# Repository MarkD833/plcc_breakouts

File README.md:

# PLCC Breakout Boards
I recently got back into designing some retro computer boards using an 8085, Z80, 68008 and 8051 chips. In order to quickly get to version 1 of a board, I needed to sort out the wiring. I created these breakout boards to allow me to patch any chip in a PLCC44, PLCC52, PLCC68 or PLCC84 package onto my memory kickstarter board (includes ROM, RAM, UART, clock, LEDs etc) to allow for rapid prototyping witout committing to a PCB design first.

There are currently 4 breakout boards.

## PLCC44 Breakout board

## PLCC52 Breakout board

## PLCC68 Breakout board

## PLCC84 Breakout board

For each breakout board, each pin on the PLCC socket is broken out into 2 pinheader (or pinsocket) contacts. There are 8 ground pins that connect to the copper pour BUT do not connect to any pins on the PLCC socket. There is no decoupling provided on the breakout board as the power and ground pins are specific to the actual device being used. 

Please see the boards folder for the Kicad design files.

## Version History

* 1.0
    * Initial Release

## License

This project is licensed under the GNU General Public License v3.0 - see the LICENSE.md file for details

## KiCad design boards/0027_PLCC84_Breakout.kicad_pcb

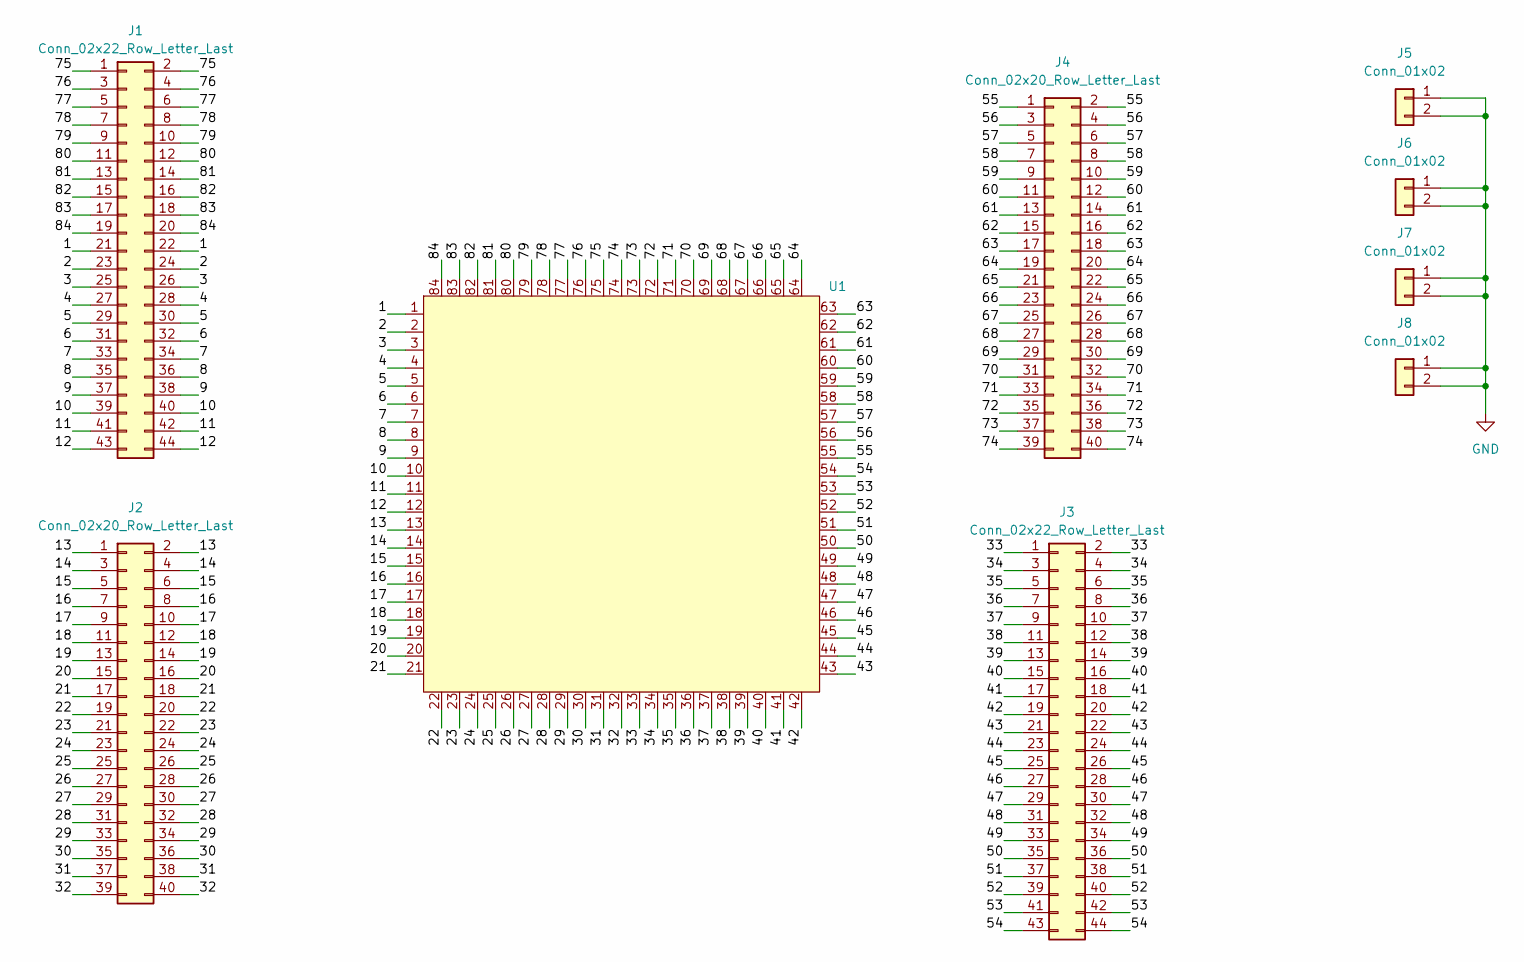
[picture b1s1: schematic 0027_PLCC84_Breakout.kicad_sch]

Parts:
J1, J3: Conn_02x22_Row_Letter_Last; PinSocket_2x22_P2.54mm_Vertical
J2, J4: Conn_02x20_Row_Letter_Last; PinSocket_2x20_P2.54mm_Vertical
J5, J6, J7, J8: Conn_01x02; PinHeader_1x02_P2.54mm_Vertical
U1: PLCC-84_THT-Socket

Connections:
/1: J1.21, J1.22, U1.1
/2: J1.23, J1.24, U1.2
/3: J1.25, J1.26, U1.3
/4: J1.27, J1.28, U1.4
/5: J1.29, J1.30, U1.5
/6: J1.31, J1.32, U1.6
/7: J1.33, J1.34, U1.7
/8: J1.35, J1.36, U1.8
/9: J1.37, J1.38, U1.9
/10: J1.39, J1.40, U1.10
/11: J1.41, J1.42, U1.11
/12: J1.43, J1.44, U1.12
/13: J2.1, J2.2, U1.13
/14: J2.3, J2.4, U1.14
/15: J2.5, J2.6, U1.15
/16: J2.7, J2.8, U1.16
/17: J2.9, J2.10, U1.17
/18: J2.11, J2.12, U1.18
/19: J2.13, J2.14, U1.19
/20: J2.15, J2.16, U1.20
/21: J2.17, J2.18, U1.21
/22: J2.19, J2.20, U1.22
/23: J2.21, J2.22, U1.23
/24: J2.23, J2.24, U1.24
/25: J2.25, J2.26, U1.25
/26: J2.27, J2.28, U1.26
/27: J2.29, J2.30, U1.27
/28: J2.31, J2.32, U1.28
/29: J2.33, J2.34, U1.29
/30: J2.35, J2.36, U1.30
/31: J2.37, J2.38, U1.31
/32: J2.39, J2.40, U1.32
/33: J3.1, J3.2, U1.33
/34: J3.3, J3.4, U1.34
/35: J3.5, J3.6, U1.35
/36: J3.7, J3.8, U1.36
/37: J3.9, J3.10, U1.37
/38: J3.11, J3.12, U1.38
/39: J3.13, J3.14, U1.39
/40: J3.15, J3.16, U1.40
/41: J3.17, J3.18, U1.41
/42: J3.19, J3.20, U1.42
/43: J3.21, J3.22, U1.43
/44: J3.23, J3.24, U1.44
/45: J3.25, J3.26, U1.45
/46: J3.27, J3.28, U1.46
/47: J3.29, J3.30, U1.47
/48: J3.31, J3.32, U1.48
/49: J3.33, J3.34, U1.49
/50: J3.35, J3.36, U1.50
/51: J3.37, J3.38, U1.51
/52: J3.39, J3.40, U1.52
/53: J3.41, J3.42, U1.53
/54: J3.43, J3.44, U1.54
/55: J4.1, J4.2, U1.55
/56: J4.3, J4.4, U1.56
/57: J4.5, J4.6, U1.57
/58: J4.7, J4.8, U1.58
/59: J4.9, J4.10, U1.59
/60: J4.11, J4.12, U1.60
/61: J4.13, J4.14, U1.61
/62: J4.15, J4.16, U1.62
/63: J4.17, J4.18, U1.63
/64: J4.19, J4.20, U1.64
/65: J4.21, J4.22, U1.65
/66: J4.23, J4.24, U1.66
/67: J4.25, J4.26, U1.67
/68: J4.27, J4.28, U1.68
/69: J4.29, J4.30, U1.69
/70: J4.31, J4.32, U1.70
/71: J4.33, J4.34, U1.71
/72: J4.35, J4.36, U1.72
/73: J4.37, J4.38, U1.73
/74: J4.39, J4.40, U1.74
/75: J1.1, J1.2, U1.75
/76: J1.3, J1.4, U1.76
/77: J1.5, J1.6, U1.77
/78: J1.7, J1.8, U1.78
/79: J1.9, J1.10, U1.79
/80: J1.11, J1.12, U1.80
/81: J1.13, J1.14, U1.81
/82: J1.15, J1.16, U1.82
/83: J1.17, J1.18, U1.83
/84: J1.19, J1.20, U1.84
GND: J5.1, J5.2, J6.1, J6.2, J7.1, J7.2, J8.1, J8.2

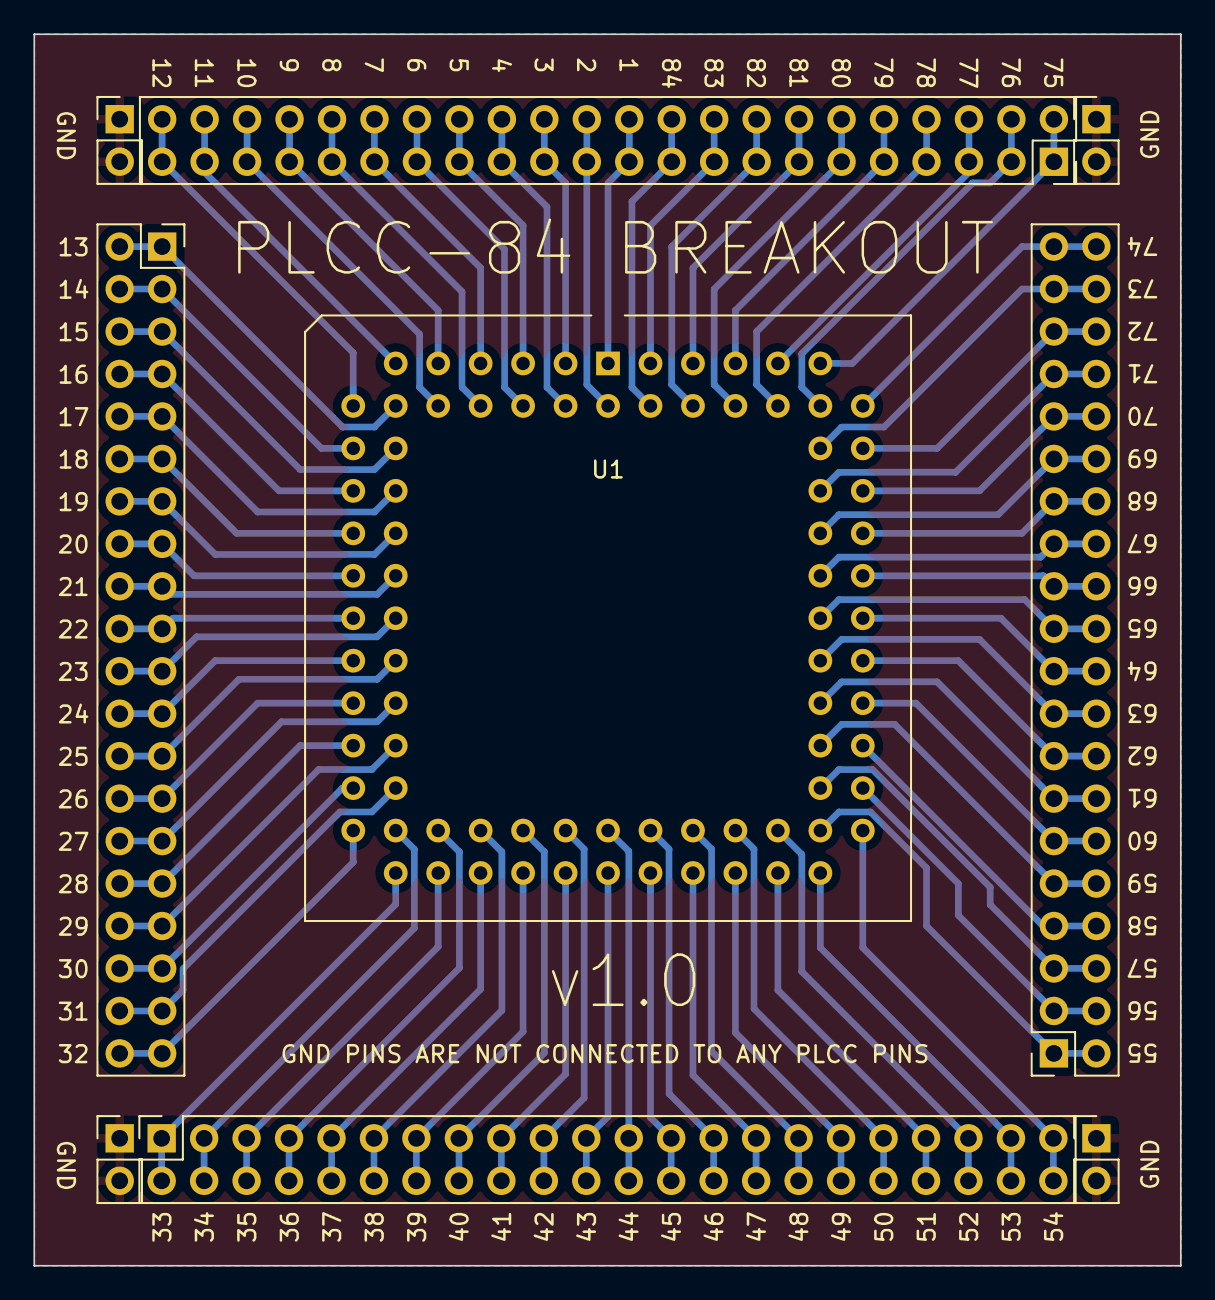
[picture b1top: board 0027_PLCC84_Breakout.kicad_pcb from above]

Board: 2 copper layers, 68.6 x 73.7 mm, 9 parts (0 on the bottom side), 85 nets.

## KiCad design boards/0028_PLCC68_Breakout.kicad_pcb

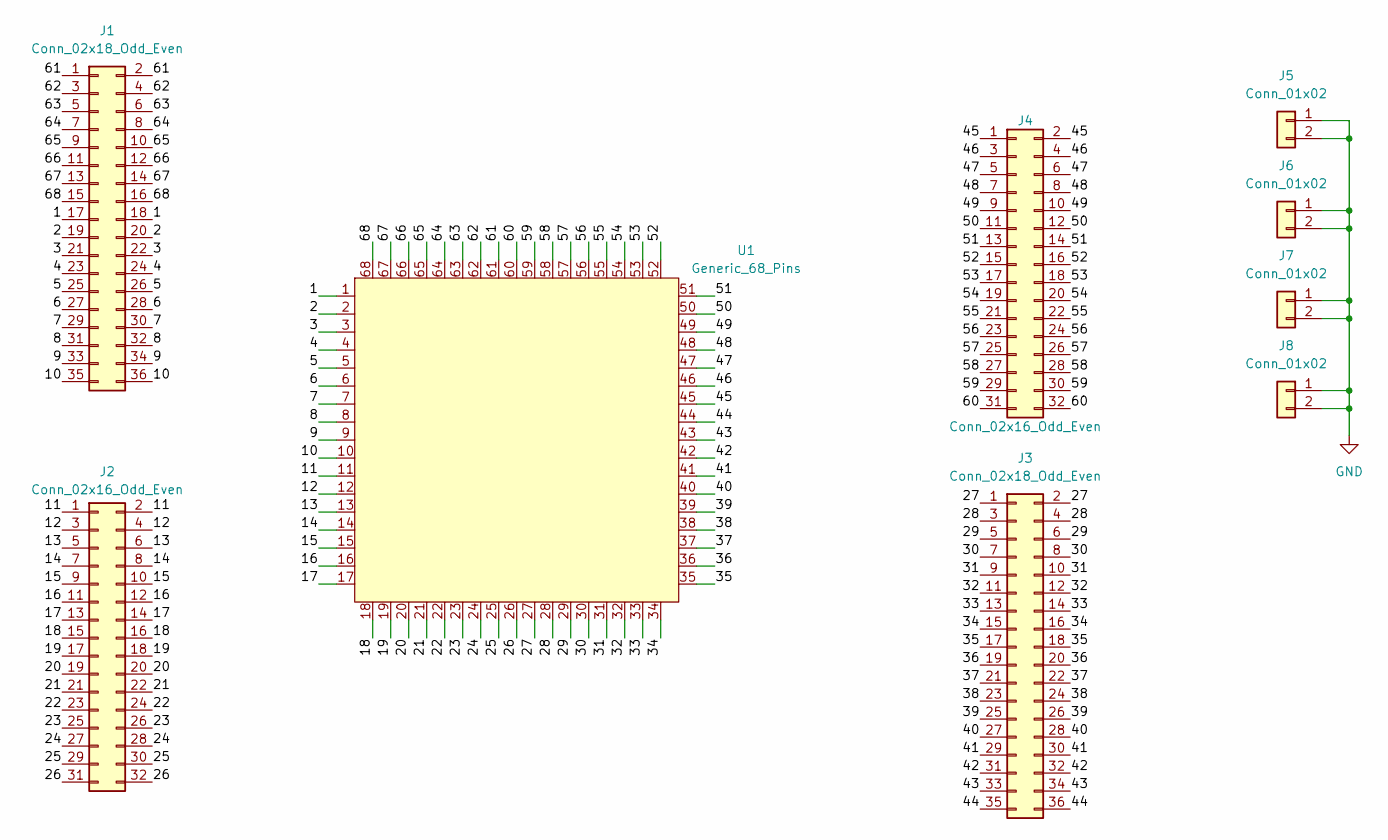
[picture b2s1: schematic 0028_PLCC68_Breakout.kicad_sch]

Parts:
J1, J3: Conn_02x18_Odd_Even; PinSocket_2x18_P2.54mm_Vertical
J2, J4: Conn_02x16_Odd_Even; PinSocket_2x16_P2.54mm_Vertical
J5, J6, J7, J8: Conn_01x02; PinHeader_1x02_P2.54mm_Vertical
U1: Generic_68_Pins; PLCC-68_THT-Socket

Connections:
/1: J1.17, J1.18, U1.1
/2: J1.19, J1.20, U1.2
/3: J1.21, J1.22, U1.3
/4: J1.23, J1.24, U1.4
/5: J1.25, J1.26, U1.5
/6: J1.27, J1.28, U1.6
/7: J1.29, J1.30, U1.7
/8: J1.31, J1.32, U1.8
/9: J1.33, J1.34, U1.9
/10: J1.35, J1.36, U1.10
/11: J2.1, J2.2, U1.11
/12: J2.3, J2.4, U1.12
/13: J2.5, J2.6, U1.13
/14: J2.7, J2.8, U1.14
/15: J2.9, J2.10, U1.15
/16: J2.11, J2.12, U1.16
/17: J2.13, J2.14, U1.17
/18: J2.15, J2.16, U1.18
/19: J2.17, J2.18, U1.19
/20: J2.19, J2.20, U1.20
/21: J2.21, J2.22, U1.21
/22: J2.23, J2.24, U1.22
/23: J2.25, J2.26, U1.23
/24: J2.27, J2.28, U1.24
/25: J2.29, J2.30, U1.25
/26: J2.31, J2.32, U1.26
/27: J3.1, J3.2, U1.27
/28: J3.3, J3.4, U1.28
/29: J3.5, J3.6, U1.29
/30: J3.7, J3.8, U1.30
/31: J3.9, J3.10, U1.31
/32: J3.11, J3.12, U1.32
/33: J3.13, J3.14, U1.33
/34: J3.15, J3.16, U1.34
/35: J3.17, J3.18, U1.35
/36: J3.19, J3.20, U1.36
/37: J3.21, J3.22, U1.37
/38: J3.23, J3.24, U1.38
/39: J3.25, J3.26, U1.39
/40: J3.27, J3.28, U1.40
/41: J3.29, J3.30, U1.41
/42: J3.31, J3.32, U1.42
/43: J3.33, J3.34, U1.43
/44: J3.35, J3.36, U1.44
/45: J4.1, J4.2, U1.45
/46: J4.3, J4.4, U1.46
/47: J4.5, J4.6, U1.47
/48: J4.7, J4.8, U1.48
/49: J4.9, J4.10, U1.49
/50: J4.11, J4.12, U1.50
/51: J4.13, J4.14, U1.51
/52: J4.15, J4.16, U1.52
/53: J4.17, J4.18, U1.53
/54: J4.19, J4.20, U1.54
/55: J4.21, J4.22, U1.55
/56: J4.23, J4.24, U1.56
/57: J4.25, J4.26, U1.57
/58: J4.27, J4.28, U1.58
/59: J4.29, J4.30, U1.59
/60: J4.31, J4.32, U1.60
/61: J1.1, J1.2, U1.61
/62: J1.3, J1.4, U1.62
/63: J1.5, J1.6, U1.63
/64: J1.7, J1.8, U1.64
/65: J1.9, J1.10, U1.65
/66: J1.11, J1.12, U1.66
/67: J1.13, J1.14, U1.67
/68: J1.15, J1.16, U1.68
GND: J5.1, J5.2, J6.1, J6.2, J7.1, J7.2, J8.1, J8.2

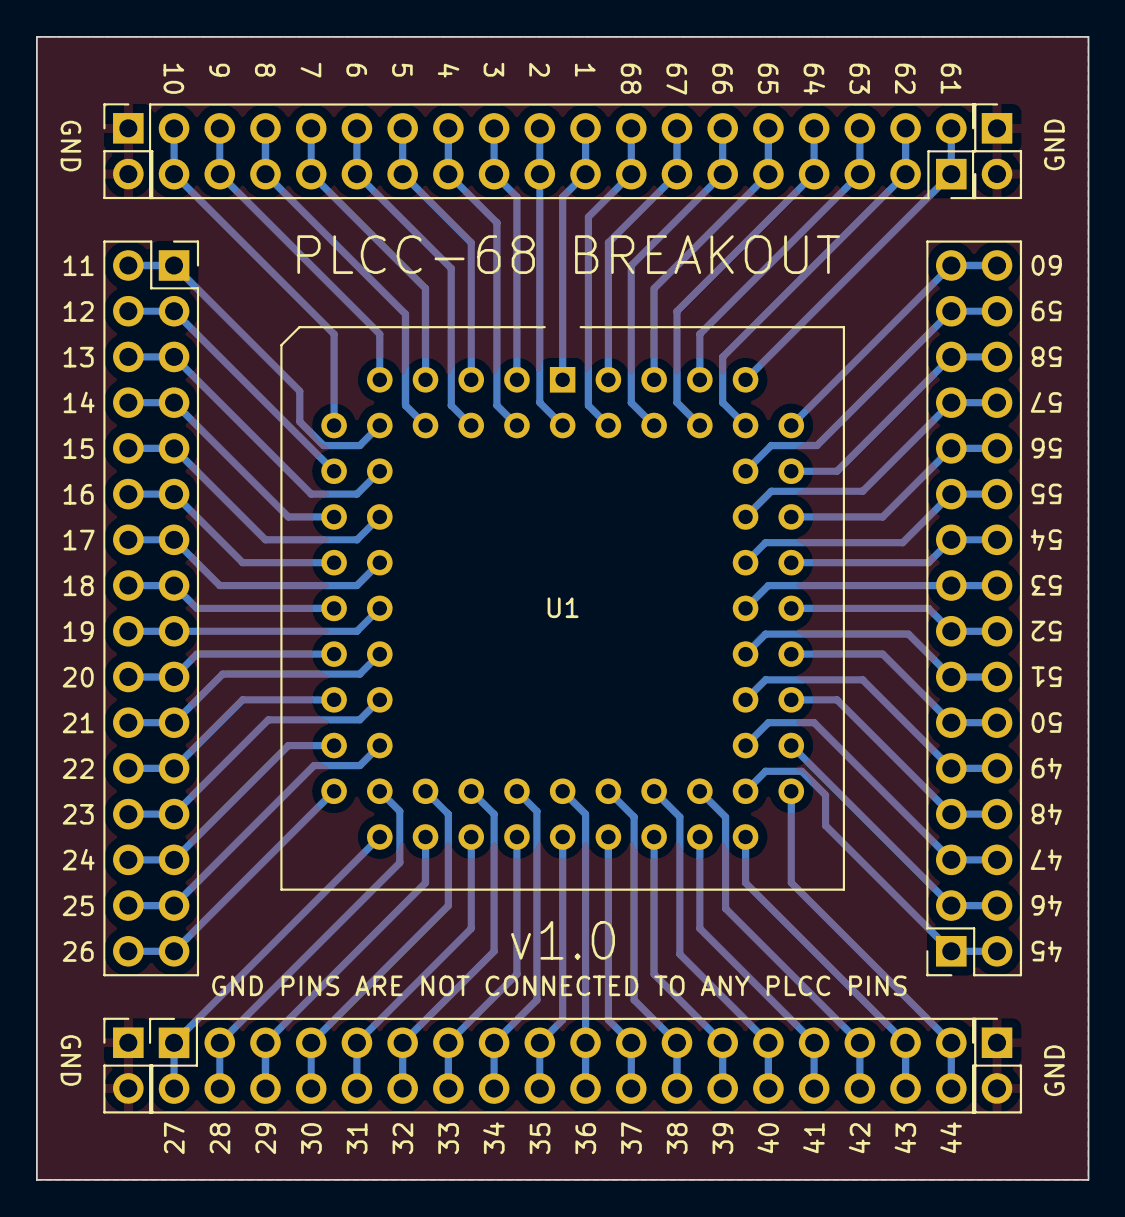
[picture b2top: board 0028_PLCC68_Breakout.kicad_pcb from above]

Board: 2 copper layers, 58.4 x 63.5 mm, 9 parts (0 on the bottom side), 69 nets.

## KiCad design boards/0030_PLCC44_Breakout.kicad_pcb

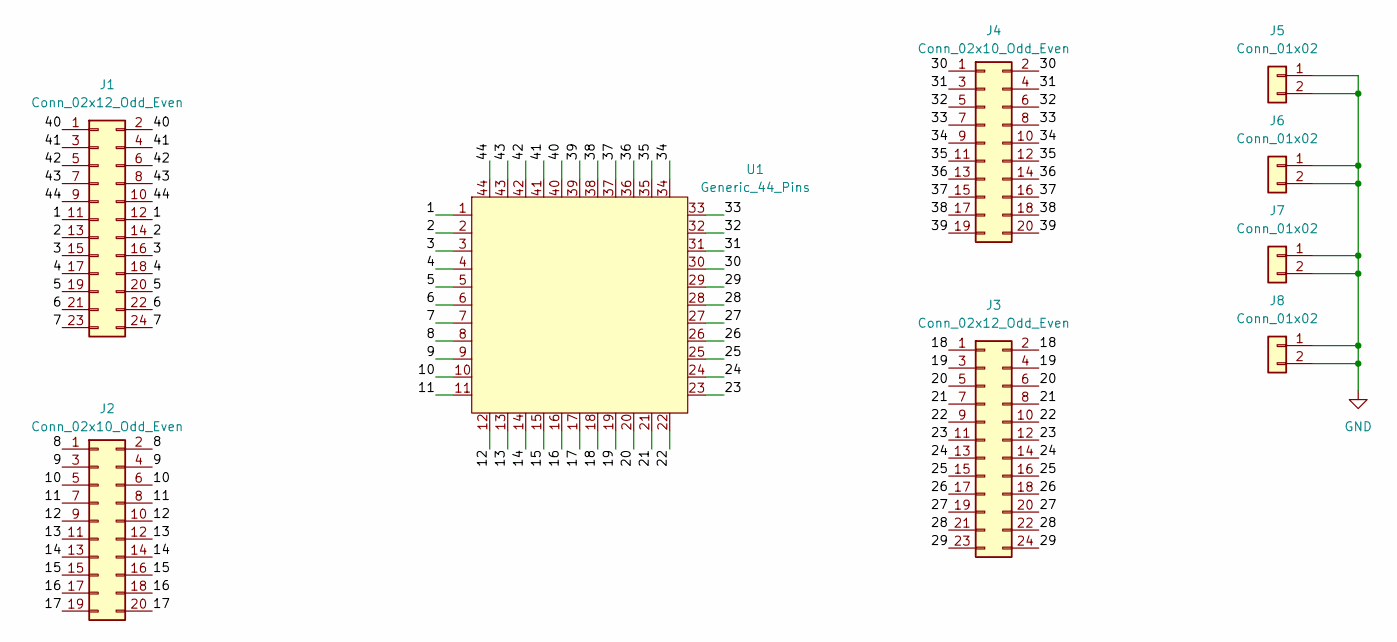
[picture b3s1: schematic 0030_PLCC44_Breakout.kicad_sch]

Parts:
J1, J3: Conn_02x12_Odd_Even; PinSocket_2x12_P2.54mm_Vertical
J2, J4: Conn_02x10_Odd_Even; PinSocket_2x10_P2.54mm_Vertical
J5, J6, J7, J8: Conn_01x02; PinHeader_1x02_P2.54mm_Vertical
U1: Generic_44_Pins; PLCC-44_THT-Socket

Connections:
/1: J1.11, J1.12, U1.1
/2: J1.13, J1.14, U1.2
/3: J1.15, J1.16, U1.3
/4: J1.17, J1.18, U1.4
/5: J1.19, J1.20, U1.5
/6: J1.21, J1.22, U1.6
/7: J1.23, J1.24, U1.7
/8: J2.1, J2.2, U1.8
/9: J2.3, J2.4, U1.9
/10: J2.5, J2.6, U1.10
/11: J2.7, J2.8, U1.11
/12: J2.9, J2.10, U1.12
/13: J2.11, J2.12, U1.13
/14: J2.13, J2.14, U1.14
/15: J2.15, J2.16, U1.15
/16: J2.17, J2.18, U1.16
/17: J2.19, J2.20, U1.17
/18: J3.1, J3.2, U1.18
/19: J3.3, J3.4, U1.19
/20: J3.5, J3.6, U1.20
/21: J3.7, J3.8, U1.21
/22: J3.9, J3.10, U1.22
/23: J3.11, J3.12, U1.23
/24: J3.13, J3.14, U1.24
/25: J3.15, J3.16, U1.25
/26: J3.17, J3.18, U1.26
/27: J3.19, J3.20, U1.27
/28: J3.21, J3.22, U1.28
/29: J3.23, J3.24, U1.29
/30: J4.1, J4.2, U1.30
/31: J4.3, J4.4, U1.31
/32: J4.5, J4.6, U1.32
/33: J4.7, J4.8, U1.33
/34: J4.9, J4.10, U1.34
/35: J4.11, J4.12, U1.35
/36: J4.13, J4.14, U1.36
/37: J4.15, J4.16, U1.37
/38: J4.17, J4.18, U1.38
/39: J4.19, J4.20, U1.39
/40: J1.1, J1.2, U1.40
/41: J1.3, J1.4, U1.41
/42: J1.5, J1.6, U1.42
/43: J1.7, J1.8, U1.43
/44: J1.9, J1.10, U1.44
GND: J5.1, J5.2, J6.1, J6.2, J7.1, J7.2, J8.1, J8.2

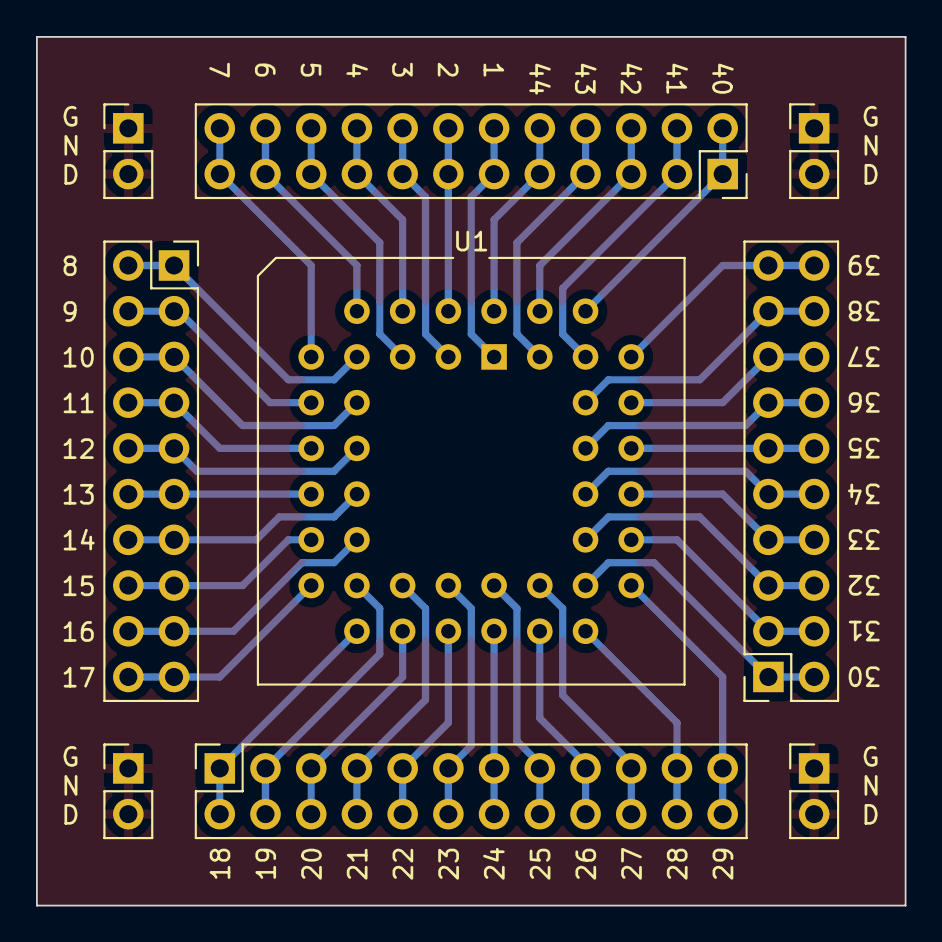
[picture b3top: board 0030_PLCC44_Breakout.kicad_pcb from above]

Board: 2 copper layers, 48.3 x 48.3 mm, 9 parts (0 on the bottom side), 45 nets.

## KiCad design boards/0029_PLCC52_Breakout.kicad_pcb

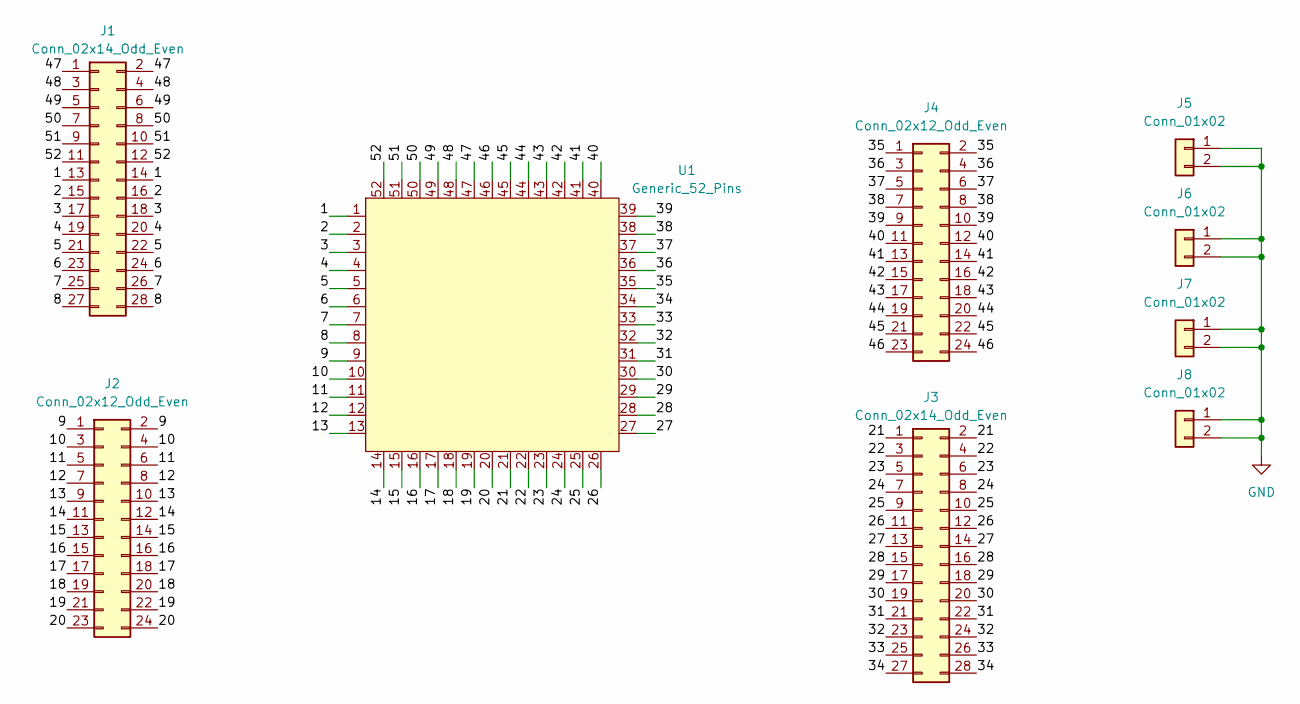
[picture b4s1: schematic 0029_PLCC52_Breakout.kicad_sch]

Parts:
J1, J3: Conn_02x14_Odd_Even; PinSocket_2x14_P2.54mm_Vertical
J2, J4: Conn_02x12_Odd_Even; PinSocket_2x12_P2.54mm_Vertical
J5, J6, J7, J8: Conn_01x02; PinHeader_1x02_P2.54mm_Vertical
U1: Generic_52_Pins; PLCC-52_THT-Socket

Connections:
/1: J1.13, J1.14, U1.1
/2: J1.15, J1.16, U1.2
/3: J1.17, J1.18, U1.3
/4: J1.19, J1.20, U1.4
/5: J1.21, J1.22, U1.5
/6: J1.23, J1.24, U1.6
/7: J1.25, J1.26, U1.7
/8: J1.27, J1.28, U1.8
/9: J2.1, J2.2, U1.9
/10: J2.3, J2.4, U1.10
/11: J2.5, J2.6, U1.11
/12: J2.7, J2.8, U1.12
/13: J2.9, J2.10, U1.13
/14: J2.11, J2.12, U1.14
/15: J2.13, J2.14, U1.15
/16: J2.15, J2.16, U1.16
/17: J2.17, J2.18, U1.17
/18: J2.19, J2.20, U1.18
/19: J2.21, J2.22, U1.19
/20: J2.23, J2.24, U1.20
/21: J3.1, J3.2, U1.21
/22: J3.3, J3.4, U1.22
/23: J3.5, J3.6, U1.23
/24: J3.7, J3.8, U1.24
/25: J3.9, J3.10, U1.25
/26: J3.11, J3.12, U1.26
/27: J3.13, J3.14, U1.27
/28: J3.15, J3.16, U1.28
/29: J3.17, J3.18, U1.29
/30: J3.19, J3.20, U1.30
/31: J3.21, J3.22, U1.31
/32: J3.23, J3.24, U1.32
/33: J3.25, J3.26, U1.33
/34: J3.27, J3.28, U1.34
/35: J4.1, J4.2, U1.35
/36: J4.3, J4.4, U1.36
/37: J4.5, J4.6, U1.37
/38: J4.7, J4.8, U1.38
/39: J4.9, J4.10, U1.39
/40: J4.11, J4.12, U1.40
/41: J4.13, J4.14, U1.41
/42: J4.15, J4.16, U1.42
/43: J4.17, J4.18, U1.43
/44: J4.19, J4.20, U1.44
/45: J4.21, J4.22, U1.45
/46: J4.23, J4.24, U1.46
/47: J1.1, J1.2, U1.47
/48: J1.3, J1.4, U1.48
/49: J1.5, J1.6, U1.49
/50: J1.7, J1.8, U1.50
/51: J1.9, J1.10, U1.51
/52: J1.11, J1.12, U1.52
GND: J5.1, J5.2, J6.1, J6.2, J7.1, J7.2, J8.1, J8.2

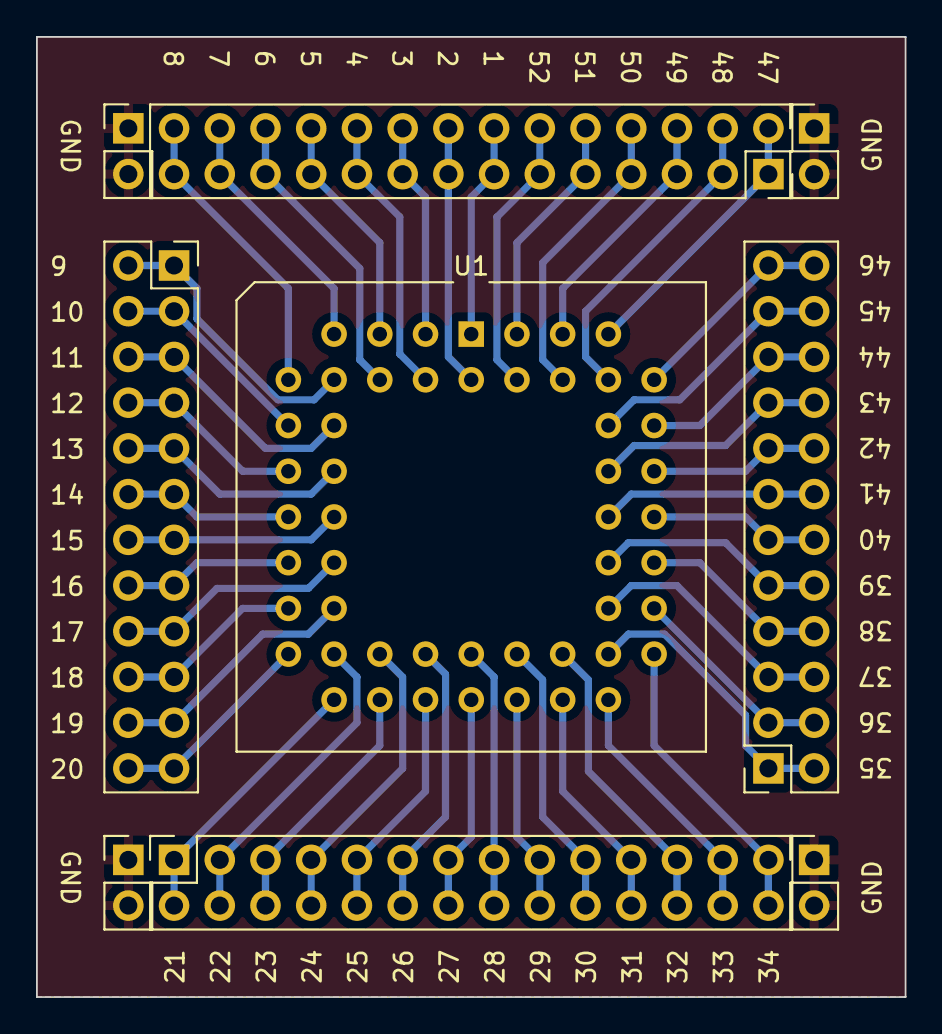
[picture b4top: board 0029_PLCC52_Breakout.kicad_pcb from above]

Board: 2 copper layers, 48.3 x 53.3 mm, 9 parts (0 on the bottom side), 53 nets.
